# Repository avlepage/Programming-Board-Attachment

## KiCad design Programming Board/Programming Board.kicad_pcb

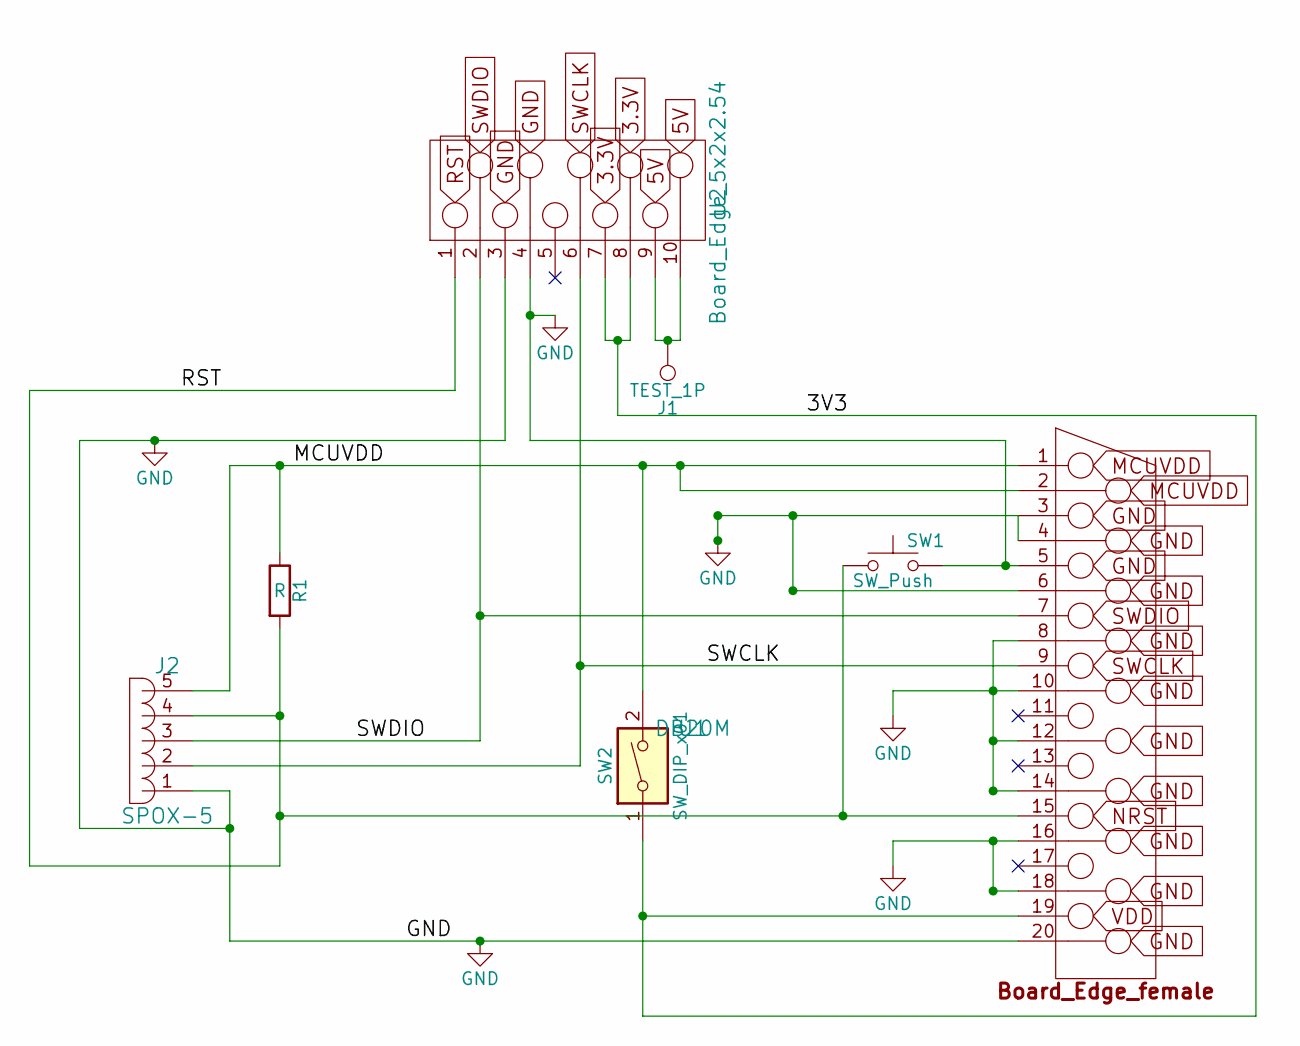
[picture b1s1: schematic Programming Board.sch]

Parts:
J1: TEST_1P; Test_Point_5V
J2: SPOX-5; Molex_SPOX-5267_22-03-5055_05x2.54mm_Straight; part_num CONN-004
R1: R; 1.7x6.5
SW1: SW_Push; Programmer_ResetButton
SW2: SW_DIP_x01; Programming_Board_Switch
U1: DB20M; Board_Edge_10x2x2.54
U2: Board_Edge_5x2x2.54; Board_Edge_Female2x5x2.54

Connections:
/3V3: SW2.1, U1.19, U2.7, U2.8
GND: J2.1, SW1.2, U1.3, U1.4, U1.5, U1.6, U1.8, U1.10, U1.12, U1.14, U1.16, U1.18, U1.20, U2.3, U2.4
MCUVDD: J2.5, R1.1, SW2.2, U1.1, U1.2
unnamed: J1.1, U2.9, U2.10
RST: J2.4, R1.2, SW1.1, U1.15, U2.1
SWCLK: J2.2, U1.9, U2.6
SWDIO: J2.3, U1.7, U2.2

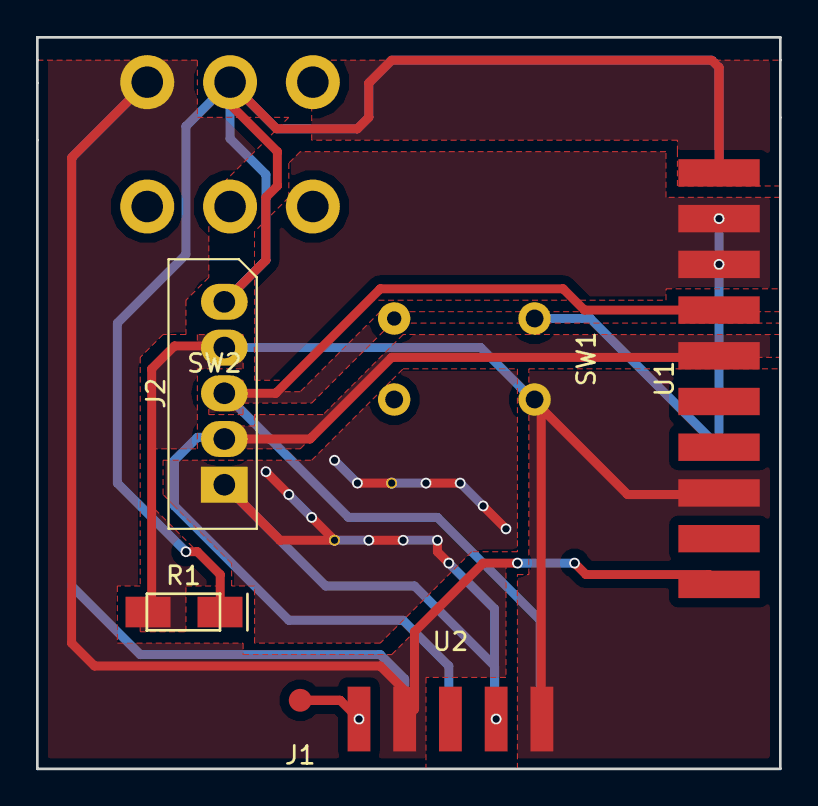
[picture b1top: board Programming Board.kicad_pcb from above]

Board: 2 copper layers, 41.3 x 40.6 mm, 7 parts (0 on the bottom side), 7 nets.

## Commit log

2017-11-04 Added Programming Board files
    Added all current programming board files to my forked repository
2017-11-30 test commit
2017-11-30 Add WARG-KiCAD submodule
2017-11-30 Update git modules
2018-01-18 Add everything
2018-01-18 PCB update
2018-01-19 Fix pad connections
